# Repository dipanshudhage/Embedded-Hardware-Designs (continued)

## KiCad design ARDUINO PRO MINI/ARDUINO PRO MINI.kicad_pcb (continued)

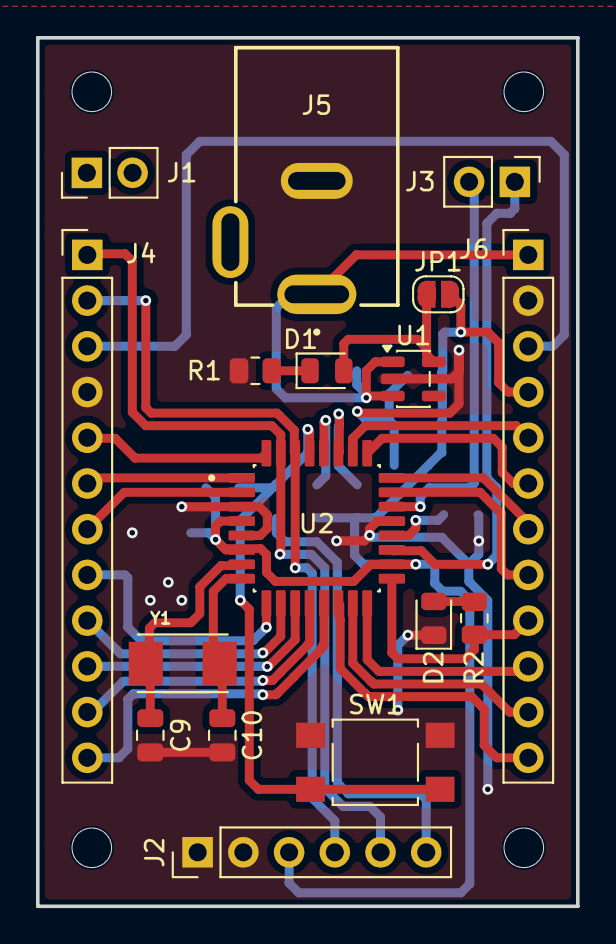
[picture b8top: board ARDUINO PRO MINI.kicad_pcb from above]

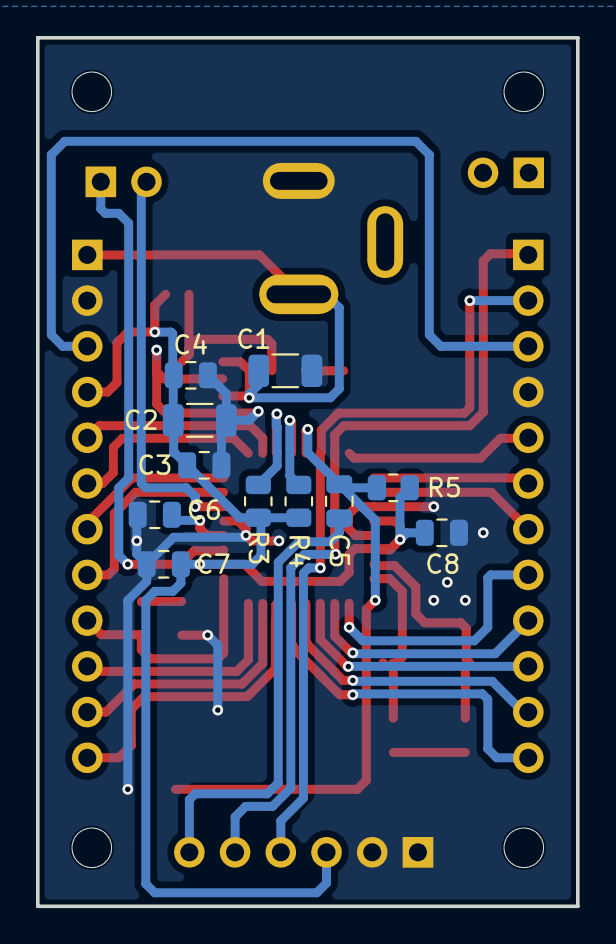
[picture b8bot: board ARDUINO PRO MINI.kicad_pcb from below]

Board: 2 copper layers, 30.0 x 48.2 mm, 32 parts (11 on the bottom side), 34 nets.
